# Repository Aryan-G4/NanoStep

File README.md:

# NanoStep - The World's Smallest Stepper Motor Driver
Redesigning the common A4988 Stepper driver motor board into an ultra-compact multi-layer PCB layout, creating the smallest bipolar Stepper motor driver ever.
Careful steps have been taken to 

wrok in progress..

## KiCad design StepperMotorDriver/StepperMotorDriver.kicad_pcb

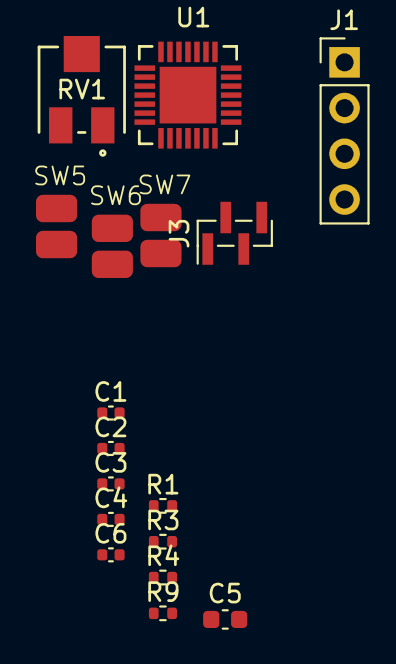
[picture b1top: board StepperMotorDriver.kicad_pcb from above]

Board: 2 copper layers, 17 parts (0 on the bottom side), 22 nets, no tracks yet.

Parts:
C1, C4: 0.22u; C_0402_1005Metric
C2, C3, C6: 0.1u; C_0402_1005Metric
C5: 4.7u; C_0603_1608Metric
J1: Conn_01x04_Pin; PinHeader_1x04_P2.54mm_Vertical
J3: Conn_01x04_Pin; PinHeader_1x04_P1.00mm_Vertical_SMD_Pin1Left
R1: 5k; R_0402_1005Metric
R3, R4: 68m; R_0402_1005Metric
R9: 10k; R_0402_1005Metric
RV1: 10k; POT_3314J
SW5, SW6, SW7: SW_Push; Pads to short
U1: A4988SETTR-T; A4988_QFN-28_ALM

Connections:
+3.3V: C4.1, R1.1, RV1.1, SW5.1, SW6.1, SW7.1, U1.15 (VDD)
+24V: C2.2, C5.1, C6.2, U1.22 (VBB1), U1.28 (VBB2)
/MS1: SW5.2, U1.9 (MS1)
/MS2: SW6.2, U1.10 (MS2)
/MS3: SW7.2, U1.11 (MS3)
/V_{REF}: RV1.2, U1.17 (REF)
GND: C1.1, C4.2, C5.2, C6.1, R3.2, R4.2, R9.2, RV1.3, U1.3 (GND), U1.13 (ROSC), U1.18 (GND), U1.29 (GND)
unnamed: J1.1, U1.24 (OUT1A)
unnamed: J1.2, U1.21 (OUT1B)
unnamed: J1.3, U1.26 (OUT2A)
unnamed: J1.4, U1.1 (OUT2B)
unnamed: J3.1, R9.1, U1.2 (~ENABLE)
unnamed: J3.2, U1.12 (~RESET)
unnamed: J3.3, U1.16 (STEP)
unnamed: J3.4, U1.19 (DIR)
unnamed: C3.2, U1.4 (CP1)
unnamed: C3.1, U1.5 (CP2)
unnamed: R4.1, U1.23 (SENSE1)
unnamed: R3.1, U1.27 (SENSE2)
unnamed: C2.1, U1.6 (VCP)
unnamed: C1.2, U1.8 (VREG)
unnamed: R1.2, U1.14 (~SLEEP)

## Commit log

2024-08-16 Added Documentation
2024-08-16 Begin Schematic design
    Added A4988 IC
2024-08-16 edited schematic
2024-08-18 Edited Schematic
    Changed main IC symbol
    Added Peripheral components
    Assigned footprints
2024-08-28 Updated Schematic
2024-08-31 COMPLETED schematic and added documentation
2024-09-12 changed schematic, assigned footprints
